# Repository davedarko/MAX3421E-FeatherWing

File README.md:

# MAX3421E-FeatherWing
USB host FeatherWing

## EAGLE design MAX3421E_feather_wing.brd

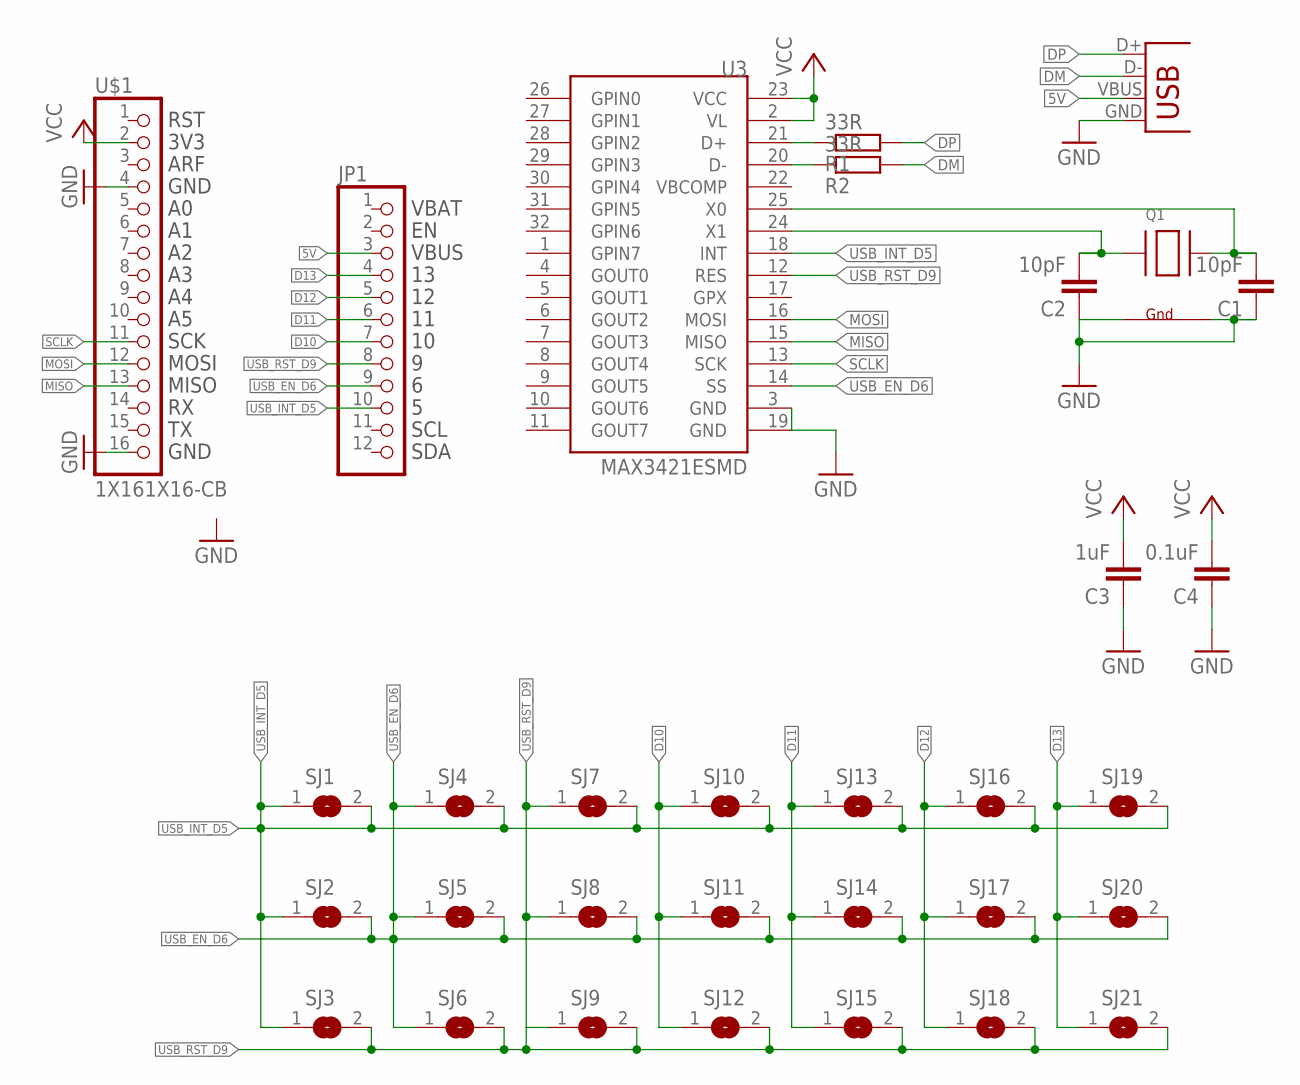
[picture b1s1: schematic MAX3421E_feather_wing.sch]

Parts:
C1, C2: 10pF; C0805K
C3: 1uF; C0805K
C4: 0.1uF; C0805K
JP1: PINHD-1X12-CB; 1X12-CB
JP3: USBUSB-A-S-NOSILK; USB-A-S-NOSILK
Q1: XTAL-4-3225; NX3225
R1, R2: 33R; R0805
SJ1, SJ2, SJ3, SJ4, SJ5, SJ6, SJ7, SJ8, SJ9, SJ10, SJ11, SJ12, SJ13, SJ14, SJ15, SJ16, SJ17, SJ18, SJ19, SJ20, SJ21: SJ
U3: MAX3421ESMD; TQFP32-5MM
U$1: 1X161X16-CB; 1X16-CB

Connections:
5V: JP1.3, JP3.VBUS
D10: JP1.7, SJ10.1, SJ11.1, SJ12.1
D11: JP1.6, SJ13.1, SJ14.1, SJ15.1
D12: JP1.5, SJ16.1, SJ17.1, SJ18.1
D13: JP1.4, SJ19.1, SJ20.1, SJ21.1
DM: JP3.D-, R2.2
DM_CR: R2.1, U3.20 (D-)
DP: JP3.D+, R1.2
DP_CR: R1.1, U3.21 (D+)
GND: C1.1, C2.1, C3.1, C4.1, JP3.GND, Q1.2 (G2), Q1.4 (G1), U3.3 (GND), U3.19 (GND), U$1.4, U$1.16
MISO: U3.15 (MISO), U$1.13
MOSI: U3.16 (MOSI), U$1.12
SCLK: U3.13 (SCK), U$1.11
USB_EN_D6: JP1.9, SJ2.2, SJ4.1, SJ5.1, SJ5.2, SJ6.1, SJ8.2, SJ11.2, SJ14.2, SJ17.2, SJ20.2, U3.14 (SS)
USB_INT_D5: JP1.10, SJ1.1, SJ1.2, SJ2.1, SJ3.1, SJ4.2, SJ7.2, SJ10.2, SJ13.2, SJ16.2, SJ19.2, U3.18 (INT)
USB_RST_D9: JP1.8, SJ3.2, SJ6.2, SJ7.1, SJ8.1, SJ9.1, SJ9.2, SJ12.2, SJ15.2, SJ18.2, SJ21.2, U3.12 (RES)
VCC: C3.2, C4.2, U3.2 (VL), U3.23 (VCC), U$1.2
X0: C1.2, Q1.3 (X2), U3.25 (X0)
X1: C2.2, Q1.1 (X1), U3.24 (X1)

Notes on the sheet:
MISO
MOSI
SCK
GND
ARF
3V3
RST
SDA
SCL
VBUS
VBAT

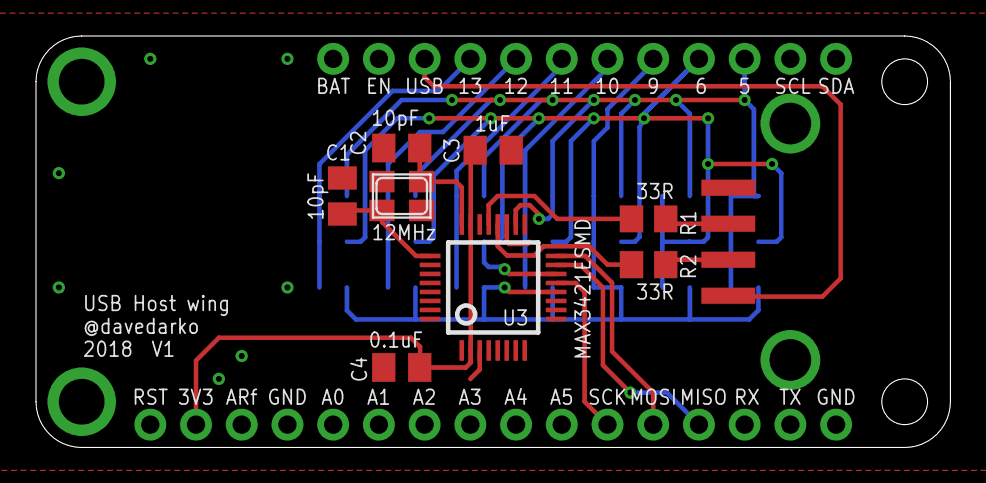
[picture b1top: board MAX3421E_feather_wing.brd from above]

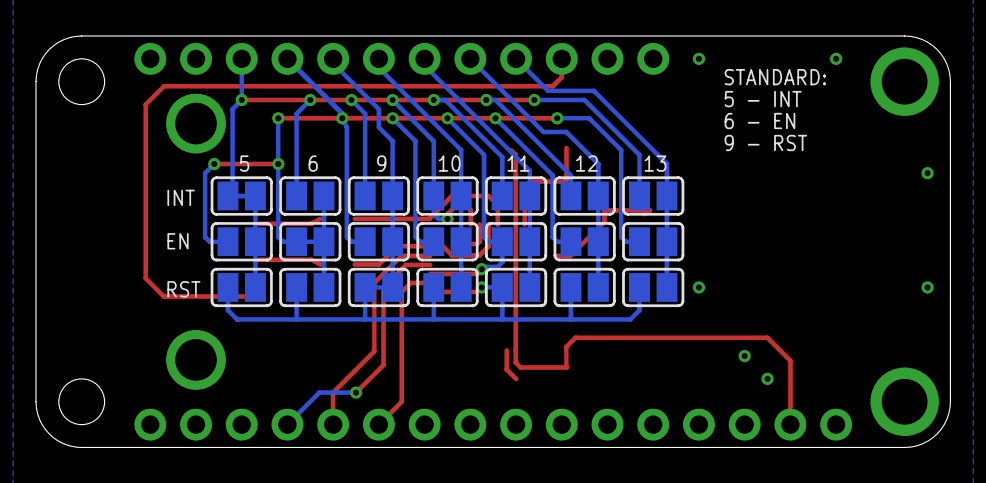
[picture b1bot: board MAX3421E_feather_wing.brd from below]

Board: 2 copper layers, 50.8 x 22.9 mm, 33 parts (21 on the bottom side), 19 nets.

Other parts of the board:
U$2: DAVEDARKO_GOLD

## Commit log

2019-01-26 design files, schematics and gerber files
2019-01-26 Create LICENSE
2019-01-26 Update LICENSE

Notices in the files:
parts and their libraries:
SparkFun-Connectors Kopie: Licensing: Creative Commons ShareAlike 4.0 International - https://creativecommons.org/licenses/by-sa/4.0
